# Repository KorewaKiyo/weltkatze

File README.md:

## A full hardware replacement for a small battery powered nightlight, which includes a bottom case, PCB + Zigbee microcontroller
Inspired by Blinkekatze

## Why?
It sounded like a fun challenge!

# More to come as the project progresses 
I've got boards but am waiting on some replacement components because I fried a couple MCUs while soldering :)

### Board view

rendered with [kicad-render](https://github.com/linalinn/kicad-render)

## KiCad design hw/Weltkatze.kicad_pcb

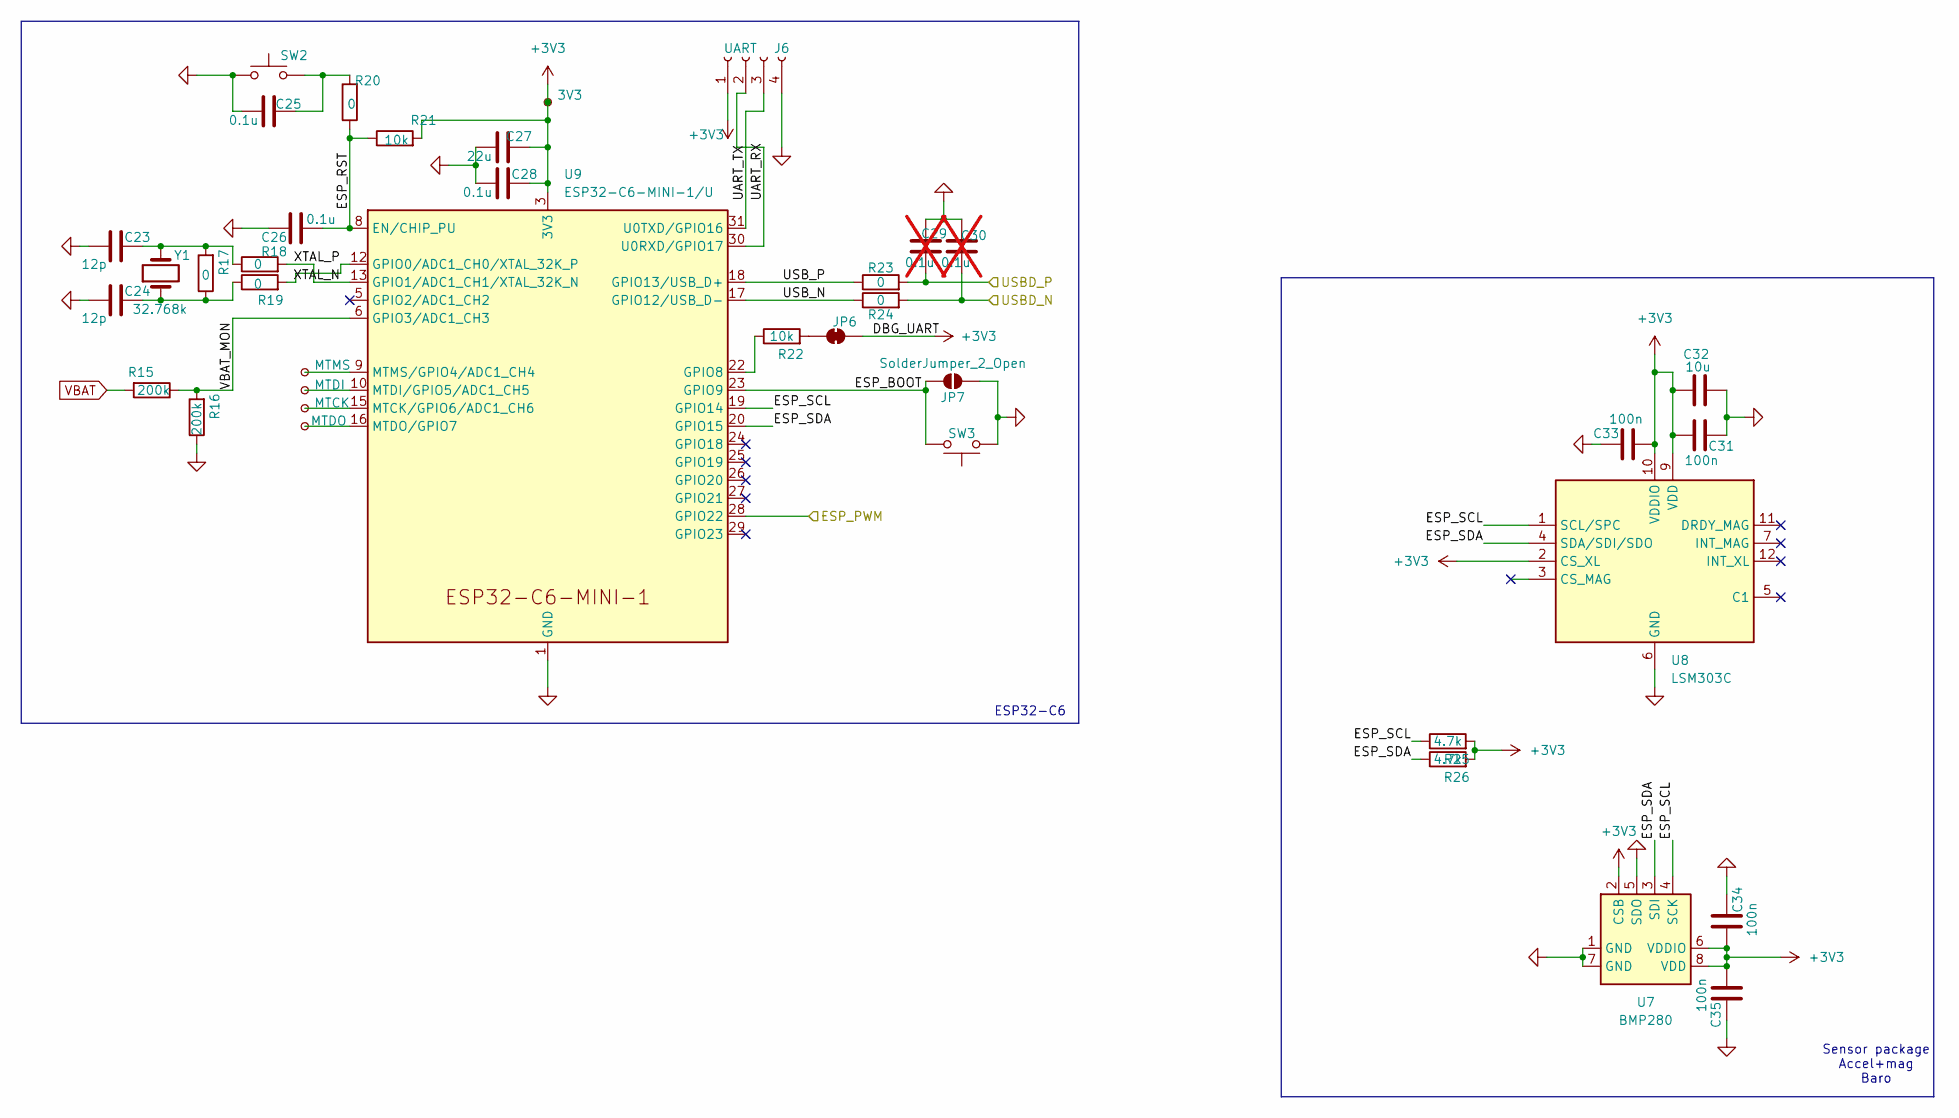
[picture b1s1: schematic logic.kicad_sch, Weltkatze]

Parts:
C23, C24: 12p; C_0402_1005Metric
C25, C26, C28: 0.1u; C_0402_1005Metric
C27: 22u; C_0805_2012Metric
C29, C30: 0.1u; C_0603_1608Metric; not fitted
C31, C33, C34, C35: 100n; C_0402_1005Metric
C32: 10u; C_0603_1608Metric
J6: UART; JST_ZH_B4B-ZR_1x04_P1.50mm_Vertical
JP6: DBG_UART; SolderJumper-2_P1.3mm_Bridged_Pad1.0x1.5mm
JP7: SolderJumper_2_Open; SolderJumper-2_P1.3mm_Open_TrianglePad1.0x1.5mm
R15, R16: 200k; R_0603_1608Metric
R17, R18, R19, R20, R23, R24: 0; R_0603_1608Metric
R21, R22: 10k; R_0603_1608Metric
R25, R26: 4.7k; R_0603_1608Metric
SW2, SW3: SW_Push; SW_SPST_CK_RS282G05A3
TP1: MTMS; TestPoint_Pad_D1.0mm
TP2: MTDI; TestPoint_Pad_D1.0mm
TP3: MTCK; TestPoint_Pad_D1.0mm
TP4: MTDO; TestPoint_Pad_D1.0mm
TP5: 3V3; TestPoint_Pad_D1.0mm
U7: BMP280; Bosch_LGA-8_2x2.5mm_P0.65mm_ClockwisePinNumbering
U8: LSM303C; LGA-12_2x2mm_P0.5mm
U9: ESP32-C6-MINI-1/U; ESP32-C6-MINI-1
Y1: 32.768k; Crystal_C26-LF_D2.1mm_L6.5mm_Horizontal

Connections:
+3V3: C27.2, C28.2, C31.1, C32.1, C33.1, C34.1, C35.1, J6.1, JP6.2 (B), R21.2, R25.2, R26.2, TP5.1, U7.2 (CSB), U7.6 (VDDIO), U7.8 (VDD), U8.2 (CS_XL), U8.9 (VDD), U8.10 (VDDIO), U9.3 (3V3); also elsewhere on the board
/LEDs/LED_DIN: U9.28 (GPIO22); also elsewhere on the board
/Logic/ESP_BOOT: JP7.1 (A), SW3.2, U9.23 (GPIO9)
/Logic/ESP_RST: C26.1, R20.1, R21.1, U9.8 (EN/CHIP_PU)
/Logic/ESP_SCL: R25.1, U7.4 (SCK), U8.1 (SCL/SPC), U9.19 (GPIO14)
/Logic/ESP_SDA: R26.1, U7.3 (SDI), U8.4 (SDA/SDI/SDO), U9.20 (GPIO15)
/Logic/UART_RX: J6.2, U9.30 (U0RXD/GPIO17)
/Logic/UART_TX: J6.3, U9.31 (U0TXD/GPIO16)
/Logic/USBD_N: C30.2, R24.2; also elsewhere on the board
/Logic/USBD_P: C29.2, R23.2; also elsewhere on the board
/Logic/USB_N: R24.1, U9.17 (GPIO12/USB_D-)
/Logic/USB_P: R23.1, U9.18 (GPIO13/USB_D+)
/Logic/VBAT_MON: R15.1, R16.2, U9.6 (GPIO3/ADC1_CH3)
/Logic/XTAL_N: R18.2, U9.13 (GPIO1/ADC1_CH1/XTAL_32K_N)
/Logic/XTAL_P: R19.2, U9.12 (GPIO0/ADC1_CH0/XTAL_32K_P)
GND: C23.1, C24.1, C25.1, C26.2, C27.1, C28.1, C29.1, C30.1, C31.2, C32.2, C33.2, C34.2, C35.2, J6.4, JP7.2 (B), R16.1, SW2.1, SW3.1, U7.1 (GND), U7.5 (SDO), U7.7 (GND), U8.6 (GND), U8.8 (GND), U9.1 (GND), U9.2 (GND), U9.11 (GND), U9.14 (GND), U9.36 (GND), U9.37 (GND), U9.38 (GND), U9.39 (GND), U9.40 (GND), U9.41 (GND), U9.42 (GND), U9.43 (GND), U9.44 (GND), U9.45 (GND), U9.46 (GND), U9.47 (GND), U9.48 (GND), U9.49 (GND), U9.50 (GND), U9.51 (GND), U9.52 (GND), U9.53 (GND); also elsewhere on the board
unnamed: C23.2, R17.2, R18.1, Y1.2
unnamed: C24.2, R17.1, R19.1, Y1.1
unnamed: C25.2, R20.2, SW2.2
unnamed: JP6.1 (A), R22.2
unnamed: R22.1, U9.22 (GPIO8)
unnamed: TP3.1, U9.15 (MTCK/GPIO6/ADC1_CH6)
unnamed: TP2.1, U9.10 (MTDI/GPIO5/ADC1_CH5)
unnamed: TP4.1, U9.16 (MTDO/GPIO7)
unnamed: TP1.1, U9.9 (MTMS/GPIO4/ADC1_CH4)
VBAT: R15.2; also elsewhere on the board

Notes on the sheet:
Sensor package Accel+mag Baro
ESP32-C6

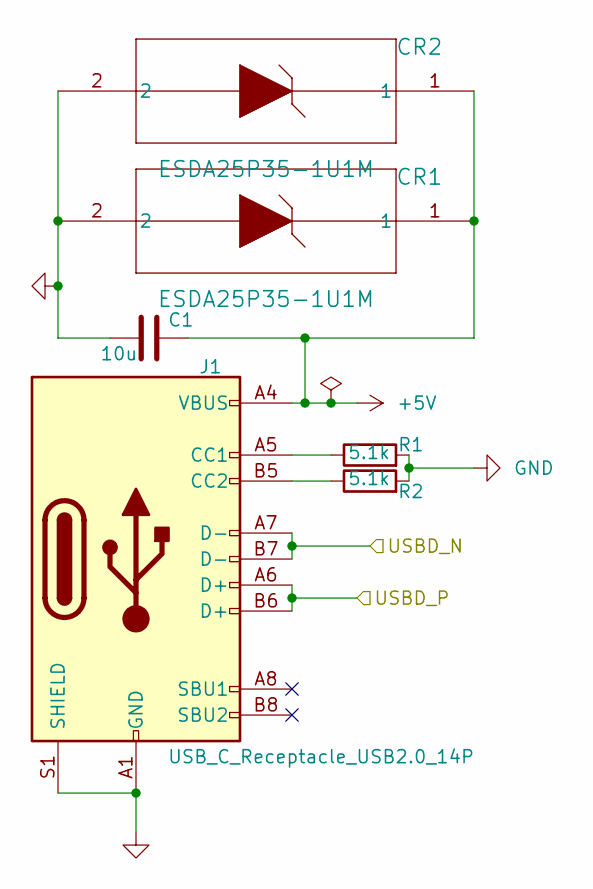
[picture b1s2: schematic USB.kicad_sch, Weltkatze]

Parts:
C1: 10u; C_0603_1608Metric
CR1, CR2: ESDA25P35-1U1M; QFN1610_STM-M
J1: USB_C_Receptacle_USB2.0_14P; USB_C_Receptacle_HCTL_HC-TYPE-C-16P-01A
R1, R2: 5.1k; R_0603_1608Metric

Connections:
+5V: C1.1, CR1.1, CR2.1, J1.A4 (VBUS), J1.A9 (VBUS), J1.B4 (VBUS), J1.B9 (VBUS); also elsewhere on the board
/Logic/USBD_N: J1.A7 (D-), J1.B7 (D-); also elsewhere on the board
/Logic/USBD_P: J1.A6 (D+), J1.B6 (D+); also elsewhere on the board
GND: C1.2, CR1.2, CR2.2, J1.A1 (GND), J1.A12 (GND), J1.B1 (GND), J1.B12 (GND), J1.S1 (SHIELD), R1.2, R2.2; also elsewhere on the board
unnamed: J1.A5 (CC1), R1.1
unnamed: J1.B5 (CC2), R2.1

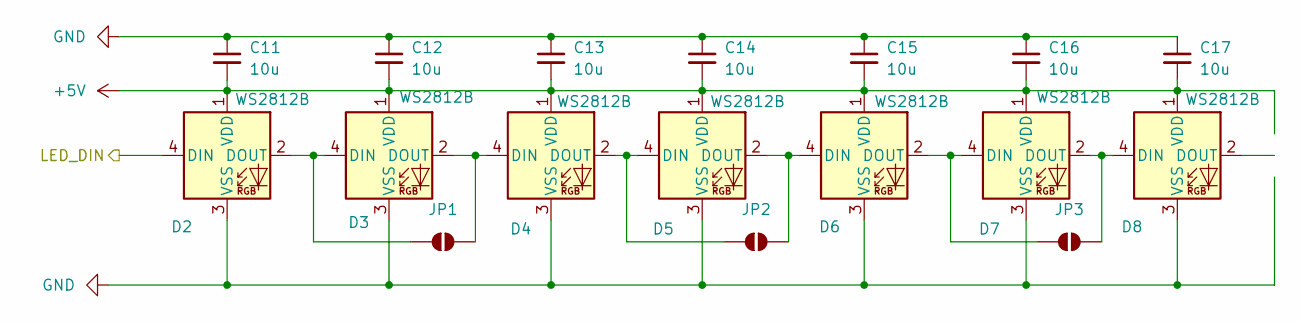
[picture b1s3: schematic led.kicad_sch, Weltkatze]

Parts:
C11, C12, C13, C14, C15, C16, C17: 10u; C_0603_1608Metric
D2, D3, D4, D5, D6, D7, D8: WS2812B; LED_WS2812B_PLCC4_5.0x5.0mm_P3.2mm
JP1, JP2, JP3: SolderJumper_2_Open; SolderJumper-2_P1.3mm_Open_TrianglePad1.0x1.5mm

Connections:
+5V: C11.2, C12.2, C13.2, C14.2, C15.2, C16.2, C17.2, D2.1 (VDD), D3.1 (VDD), D4.1 (VDD), D5.1 (VDD), D6.1 (VDD), D7.1 (VDD), D8.1 (VDD); also elsewhere on the board
/LEDs/LED_DIN: D2.4 (DIN); also elsewhere on the board
GND: C11.1, C12.1, C13.1, C14.1, C15.1, C16.1, C17.1, D2.3 (VSS), D3.3 (VSS), D4.3 (VSS), D5.3 (VSS), D6.3 (VSS), D7.3 (VSS), D8.3 (VSS); also elsewhere on the board
unnamed: D2.2 (DOUT), D3.4 (DIN), JP1.1 (A)
unnamed: D3.2 (DOUT), D4.4 (DIN), JP1.2 (B)
unnamed: D4.2 (DOUT), D5.4 (DIN), JP2.1 (A)
unnamed: D5.2 (DOUT), D6.4 (DIN), JP2.2 (B)
unnamed: D6.2 (DOUT), D7.4 (DIN), JP3.1 (A)
unnamed: D7.2 (DOUT), D8.4 (DIN), JP3.2 (B)

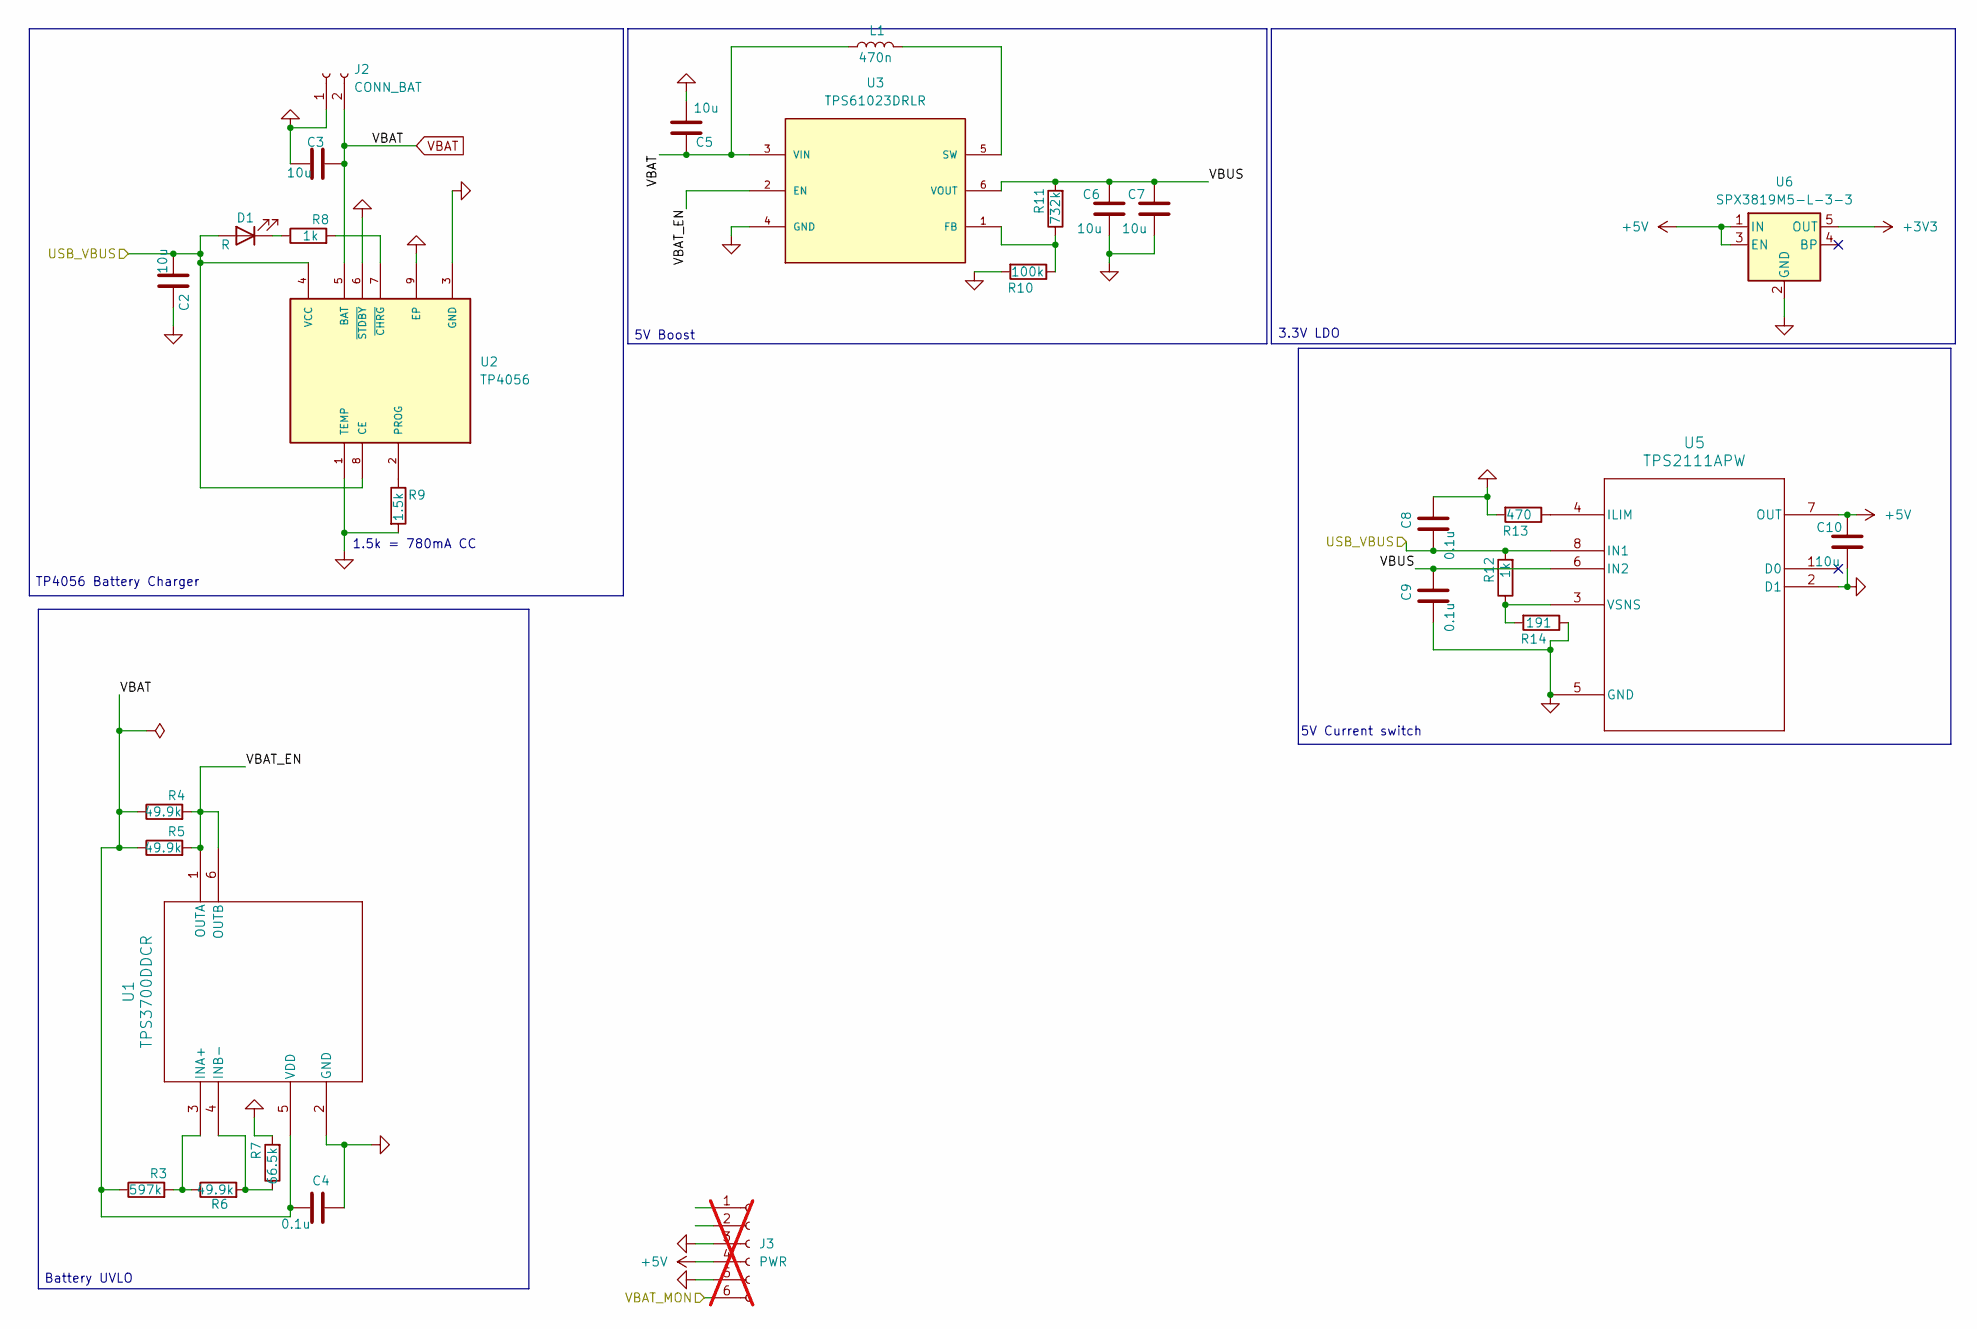
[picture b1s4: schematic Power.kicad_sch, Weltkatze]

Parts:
C2, C3, C5, C6, C7, C10: 10u; C_0603_1608Metric
C4, C8, C9: 0.1u; C_0402_1005Metric
D1: R; LED_0603_1608Metric
J2: CONN_BAT; JST_XH_B2B-XH-A_1x02_P2.50mm_Vertical
J3: PWR; JST_ZH_B6B-ZR_1x06_P1.50mm_Vertical; not fitted
L1: 470n; L_0805_2012Metric
R3: 597k; R_0603_1608Metric
R4, R5, R6: 49.9k; R_0603_1608Metric
R7: 66.5k; R_0603_1608Metric
R8, R12: 1k; R_0603_1608Metric
R9: 1.5k; R_0603_1608Metric
R10: 100k; R_0603_1608Metric
R11: 732k; R_0603_1608Metric
R13: 470; R_0603_1608Metric
R14: 191; R_0603_1608Metric
U1: TPS3700DDCR; DDC6_TEX-M
U2: TP4056; SOP127P600X175-9N
U3: TPS61023DRLR; DRL0006A; MANUFACTURER_PART_NUMBER TPS61023DRLR
U5: TPS2111APW; PW8
U6: SPX3819M5-L-3-3; SOT-23-5

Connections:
+3V3: U6.5 (OUT); also elsewhere on the board
+5V: C10.1, J3.4, U5.7 (OUT), U6.1 (IN), U6.3 (EN); also elsewhere on the board
/Power/USB_VBUS: C2.1, C8.1, D1.2 (A), R12.2, U2.4 (VCC), U2.8 (CE), U5.8 (IN1)
/Power/VBAT_EN: R4.2, R5.2, U1.1 (OUTA), U1.6 (OUTB), U3.2 (EN)
/Power/VBUS: C6.1, C7.1, C9.2, R11.2, U3.6 (VOUT), U5.6 (IN2)
GND: C2.2, C3.2, C4.2, C5.2, C6.2, C7.2, C8.2, C9.1, C10.2, J2.1, J3.3, J3.5, R7.2, R9.2, R10.2, R13.2, R14.1, U1.2 (GND), U2.1 (TEMP), U2.3 (GND), U2.6 (~STDBY), U2.9 (EP), U3.4 (GND), U5.2 (D1), U5.5 (GND), U6.2 (GND); also elsewhere on the board
unnamed: D1.1 (K), R8.1
unnamed: R3.2, R6.1, U1.3 (INA+)
unnamed: R6.2, R7.1, U1.4 (INB-)
unnamed: R9.1, U2.2 (PROG)
unnamed: R8.2, U2.7 (~CHRG)
unnamed: R10.1, R11.1, U3.1 (FB)
unnamed: L1.2, U3.5 (SW)
unnamed: R13.1, U5.4 (ILIM)
unnamed: R12.1, R14.2, U5.3 (VSNS)
VBAT: C3.1, C4.1, C5.1, J2.2, L1.1, R3.1, R4.1, R5.1, U1.5 (VDD), U2.5 (BAT), U3.3 (VIN); also elsewhere on the board

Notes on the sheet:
5V Boost
TP4056 Battery Charger
Battery UVLO
3.3V LDO
1.5k = 780mA CC
5V Current switch

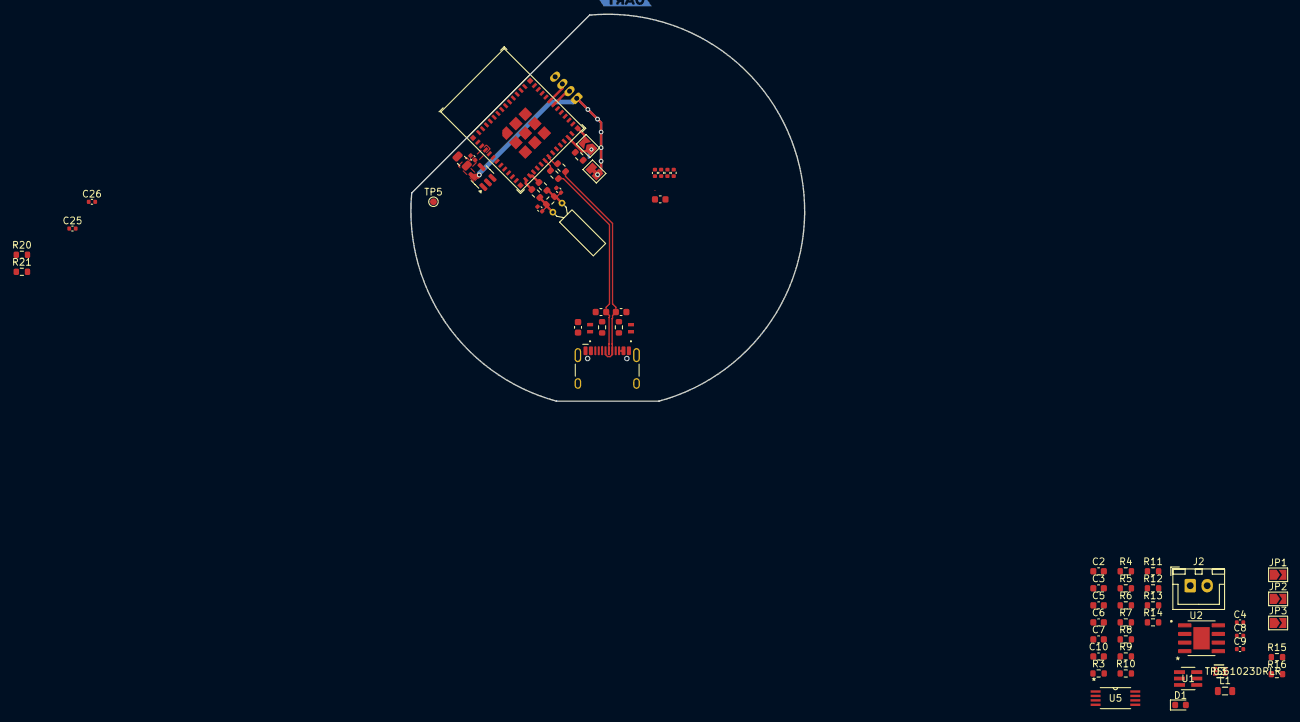
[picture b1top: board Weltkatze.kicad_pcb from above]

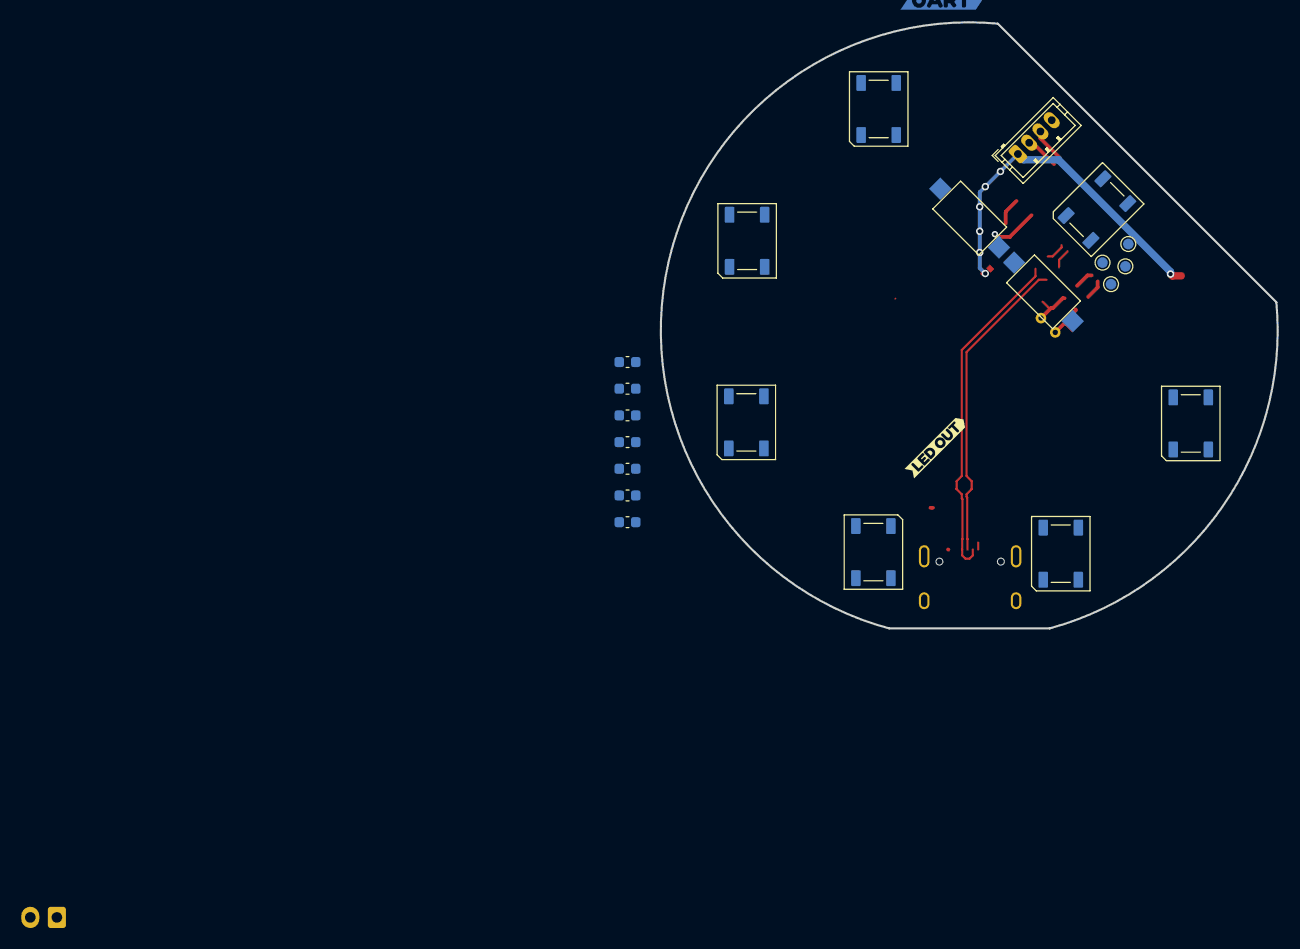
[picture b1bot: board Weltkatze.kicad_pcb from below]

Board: 2 copper layers, 58.0 x 57.0 mm, 89 parts (23 on the bottom side), 45 nets.

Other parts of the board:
kibuzzard-67CB17AB: G***; kibuzzard-67CB17AB
kibuzzard-698E3F4A: G***; kibuzzard-698E3F4A

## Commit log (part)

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2024-10-08 Start working on ESP32 implementation
    This commit starts working on getting a working ESP32 implemented
    Need to implement power stages.
2024-10-08 blep
2025-02-21 Start actual work
    I've settled on the ESP32C6, as the SEEED Xiao board based on this chipset works great. So I've started work on implementing that
2025-02-24 Replace case, start on Power stages
    I've replaced the case STL with one that's better in every way, it prints faster, doesn't need supports, and the holder for the diffuser is better,
    I may still tweak the design but I'm happy with it for now.
2025-02-24 Remove unneeded symbols
2025-02-24 Add new symbols
2025-02-24 Finish power stage, work on other stages
    Power stage should be finalised, I've updated LED stage to include a solder jumper, to allow up to half of the LEDs to be removed in the case of power/cost savings
2025-02-25 Work on footprinting and PCB
2025-02-25 Footprinting, begin layout
    I've assigned all the footprints except a few, so I've started on layout.
2025-03-05 Rest of the owl
    Finish major layout, minor tweaks can be made
    E.g. rotating the LEDs so they look pretty
    Still need to make it so the inner PCB is manufacturable
2025-03-05 I'm actually really stupid.
    I made the board sized for a RADIUS of 60mm
    and not a DIAMETER of 60mm like the damn fusion model.
2025-03-10 V1 REV1 Final!
    I consider this design finished, as such I've submitted it to JLCPCB
    I converted to a 6L pcb because its cheaper, in.3 and in.4 have no copper
2025-03-12 rev1.5
    Update to use 6 layers, inc one for 5V
    Can possibly eliminate all front copper but i like how it looks
2025-04-29 Minor reroute
    Minor reroute of traces, utilises all 6 layers effectively now.
    Also reduces some issues with USB going through multiple layers unnecessarily
2025-12-16 Update to kicad v9
2026-02-10 Redesign work
    I'm going towards a single-sided minimum viable design, so that I only need to place and hotplate one side to verify function, before adding things like battery and USB by hand.

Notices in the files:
parts and their libraries:
COPYRIGHT: Copyright (C) 2022 Ultra Librarian. All rights reserved.
